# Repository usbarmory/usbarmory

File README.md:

Introduction
============

The USB armory is an open source hardware design, implementing a compact secure
computer.

This repository is aimed towards developers, if you wish to purchase a USB
armory board please see the [ordering information](https://github.com/usbarmory/usbarmory/wiki/Ordering-information).

Authors
=======

Andrea Barisani  
andrea@inversepath.com  

Andrej Rosano  
andrej@inversepath.com  

Daniele Bianco  
daniele@inversepath.com  

Documentation
=============

The main documentation can be found on the
[project wiki](https://github.com/usbarmory/usbarmory/wiki).

Board models
============

* [USB armory Mk II LAN](https://github.com/usbarmory/usbarmory/wiki/Mk-II-LAN)

* [USB armory Mk II](https://github.com/usbarmory/usbarmory/wiki/Mk-II-Introduction)

* USB armory Mk I

License
=======

USB armory | https://github.com/usbarmory/usbarmory  
Copyright (c) The USB armory authors

This is an open hardware design licensed under the terms of the CERN Open
Hardware Licence, see board revisions for applicable versions.

This source is distributed WITHOUT ANY EXPRESS OR IMPLIED WARRANTY, INCLUDING
OF MERCHANTABILITY, SATISFACTORY QUALITY AND FITNESS FOR A PARTICULAR PURPOSE.

Please see LICENSE files in each source subdirectory for applicable conditions.

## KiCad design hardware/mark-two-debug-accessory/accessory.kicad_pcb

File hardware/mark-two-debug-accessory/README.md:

USB armory Mk II debug accessory
================================

The USB armory is an open source hardware design, implementing a flash drive
sized computer.

The USB armory Mk II exposes a USB Type-C receptacle, which allows through the
so called USB-C 'debug accessory mode' to route analog/debug signals over its
connector, the USB armory Mk II design leverages on this to break out UART,
SPI, I²C, CAN (pre-transceiver), GPIOs connections to/from its application
processor.

The debug accessory board allows to access UART and GPIO signals through USB,
without requiring probes, through an FTDI FT4232H. This allows, for example,
access to the USB armory Mk II serial console without wires or probes, natively
using only USB cables. All other interfaces can be accessed through dedicated
breakout through holes.

This repository is aimed towards developers, if you wish to purchase a USB
armory board please see the [USB armory documentation](https://github.com/usbarmory/usbarmory/wiki).

PCB Information
===============

2 layers, 0.80mm thickness, top only components  
Outer layers 0.5 oz base copper foil  
Inner layers   1 oz base copper foil  
width (X) 45.65 mm, height (Y) 25.90 mm  
Red soldermask, white component legend

[Bill of materials](https://usbarmory.github.io/BOM/usbarmory-mark-two-debug-accessory.html)

DRC information
---------------

Minimum track width:            0.127 mm  
Minimum via diameter:           0.450 mm  
Outer layer track width:        0.127 mm  
Outer layer isolation distance: 0.127 mm  
Outer layer annular ring:       0.100 mm  
Smallest final hole (plated):   0.150 mm

Errata
------

The silkscreen labels for `3.3V` and `5V` are inverted on all rev v1 PCBs, see
this [issue](https://github.com/usbarmory/usbarmory/issues/68).

USB armory Mk II debug I/Os
===========================

*NOTE*: the connection between the debug accessory and the target is supported
only with the same orientation for both top layers (side with components for
the accessory, side with LEDs for the USB armory).

The following table summarizes the available configurations on the USB armory
Mk II through debug accessory mode, which are exposed on its Type-C receptacle
port.

|  USB-C pin   | MUX mode ALT0 | MUX mode ALT8 | MUX mode ALT2 | MUX mode ALT5 |
|:-------------|---------------|---------------|---------------|---------------|
| SSTXp1 (A2)  | UART2_TX      | ECSPI3_SSO¹   | I2C4_SCL¹     | GPIO1_IO20    |
| SSTXn1 (A3)  | UART2_RX      | ECSPI3_SCLK¹  | I2C4_SDA¹     | GPIO1_IO21    |
| SSRXp1 (B11) | UART2_RTS_B   | ECSPI3_MISO¹  | FLEXCAN2_RX¹  | GPIO1_IO23    |
| SSRXn1 (B10) | UART2_CTS_B   | ECSPI3_MOSI¹  | FLEXCAN2_TX¹  | GPIO1_IO22    |
| SSRXp2 (A11) | UART4_TX      | ECSPI2_SCLK   | I2C1_SCL      | GPIO1_IO28    |
| SSTXn2 (B3)  | UART4_RX      | ECSPI2_SSO    | I2C1_SDA      | GPIO1_IO29    |
| SSRXn2 (A10) | UART5_TX~     | ECSPI2_MOSI   | I2C2_SCL      | GPIO1_IO30    |
| SSTXp2 (B2)  | UART5_RX~     | ECSPI2_MISO   | I2C2_SDA      | GPIO1_IO31    |

¹ Only on USB armory Mk II boards mounting i.MX6UL SoC, not available on
  versions mounting the i.MX6ULZ.

Serial console
--------------

When running the [USB armory Debian base image](https://github.com/usbarmory/usbarmory-debian-base_image/releases)
the serial console (UART2) can be accessed, with the debug accessory jumper set to UART
position, as follows (example on Linux host with picocom):

```
picocom -b 115200 -eb /dev/ttyUSB2 --imap lfcrlf
```

Debug accessory jumper settings
===============================

Power source
------------

The debug accessory always acts as a power source and is meant to be connected
exclusively to the USB armory Mk II Type-C receptacle port. The USB armory Mk
II Type-C can be safely plugged on a different receptacle as the board can
handle two power sources simultaneously.

It is not recommended to connect the debug accessory to anything other than the
USB armory Mk II, however in case this happens compliant Type-C receptacles
should handle the situation gracefully¹ without concerns.

¹ USB Type-C Cable and Connector Specification (1.3, 2017-07-14):
  "Legacy hosts/chargers that by default source VBUS when connected using any
  legacy USB connector (Standard-A, Micro-B, etc.) to USB Type-C cable or adapter
  are exempted from these two requirements."

I/O mode
--------

The GPIO and UART functions can be used directly using the FTDI FT4232H USB
interface accessible on the Micro USB Type-B connector, all other modes can be
accessed using the exposed breakout through holes.

The following table illustrates the required jumper positions and interfaces
for each available I/O mode.

| Mode  | GPIO¹ | Interface
|:------|-------|-----------------------------------|
| GPIO  |  GPIO | FTDI MPSSE mode on [A,B]DBUS[4-7] |
| UART2 | !GPIO | FTDI RS232 mode on CDBUS[0-3]     |
| UART4 | !GPIO | FTDI RS232 mode on BDBUS[0-1]     |
| UART5 | !GPIO | FTDI RS232 mode on ADBUS[0-1]     |
| SPI2  |  N/A² | through holes: A11, B3, A10, B2   |
| SPI3  |  N/A² | through holes: A2,  A3, B11, B10  |
| I2C1  |  N/A² | through holes: A11, B3            |
| I2C2  |  N/A² | through holes: A10, B2            |
| I2C4  |  N/A² | through holes: A2,  A3            |
| CAN2  |  N/A² | through holes: B11, B10           |

¹ The GPIO header position refers to termination either of the two pins facing
  the "GPIO" label (GPIO position, pins towards positions 3 and 2) or the
  opposite position (!GPIO position, pins towards positions 2 and 1).

² Any position can be used as the FTDI is not used in such mode.

Pin assignment: GPIO
====================

|  USB-C pin   | i.MX6UL pin | FTDI pin | FTDI MPSSE |
|:-------------|-------------|----------|------------|
| SSTXp1 (A2)  | GPIO1_IO20  | BDBUS6   | #B GPIOL2  |
| SSTXn1 (A3)  | GPIO1_IO21  | BDBUS7   | #B GPIOL3  |
| SSRXp1 (B11) | GPIO1_IO23  | BDBUS5   | #B GPIOL1  |
| SSRXn1 (B10) | GPIO1_IO22  | BDBUS4   | #B GPIOL0  |
| SSRXp2 (A11) | GPIO1_IO28  | ADBUS4   | #A GPIOL0  |
| SSTXn2 (B3)  | GPIO1_IO29  | ADBUS7   | #A GPIOL3  |
| SSRXn2 (A10) | GPIO1_IO30  | ADBUS5   | #A GPIOL1  |
| SSTXp2 (B2)  | GPIO1_IO31  | ADBUS6   | #A GPIOL2  |

Pin assignment: UART2
=====================

|  USB-C pin   | i.MX6UL pin  | FTDI pin | FTDI MPSSE |
|:-------------|--------------|----------|------------|
| SSTXp1 (A2)  | UART2_TX     | CDBUS1   | #C RXD     |
| SSTXn1 (A3)  | UART2_RX     | CDBUS0   | #C TXD     |
| SSRXp1 (B11) | UART2_RTS_B¹ | CDBUS3   | #C CTS     |
| SSRXn1 (B10) | UART2_CTS_B¹ | CDBUS2   | #C RTS     |

¹ On USB armory Mk II rev. β see the [related errata](https://github.com/usbarmory/usbarmory/wiki/Errata-(Mk-II)#errata-inverted-uart-rtscts-signals-resolved-with-workaround).

Pin assignment: UART4
=====================

|  USB-C pin   | i.MX6UL pin | FTDI pin | FTDI MPSSE |
|:-------------|-------------|----------|------------|
| SSRXp2 (A11) | UART4_TX    | BDBUS1   | #B RXD     |
| SSTXn2 (B3)  | UART4_RX    | BDBUS0   | #B TXD     |

Pin assignment: UART5
=====================

|  USB-C pin   | i.MX6UL pin | FTDI pin | FTDI MPSSE |
|:-------------|-------------|----------|------------|
| SSRXn2 (A10) | UART5_TX    | ADBUS1   | #A RXD     |
| SSTXp2 (B2)  | UART5_RX    | ADBUS0   | #A TXD     |

Physical access: UART2
======================

When no debug accessory is available, the serial console (UART2) can be also
accessed with a USB-C plug breakout and a USB to 3.3 TTL serial cable with the
following configuration.

|  PIN   | Config          |
|:-------|-----------------|
| A4, A5 | 56 kOhm         |
| B4, B5 | 56 kOhm         |
| A2, A3 | 3.3V UART TX/RX |
| A4     | 5V              |
| A1     | GND             |

License
=======

USB armory | https://github.com/usbarmory/usbarmory  
Copyright (c) The USB armory authors

This is an open hardware design licensed under the terms of the CERN Open
Hardware Licence (OHL) v1.2.

You may redistribute and modify this documentation under the terms of the CERN
OHL v.1.2 (http://ohwr.org/cernohl). This documentation is distributed WITHOUT
ANY EXPRESS OR IMPLIED WARRANTY, INCLUDING OF MERCHANTABILITY, SATISFACTORY
QUALITY AND FITNESS FOR A PARTICULAR PURPOSE. Please see the CERN OHL v.1.2 for
applicable conditions.

The following exceptions apply:

- `../lib.snapeda`: all files in this directory are imported or modified
  from SnapEDA symbols and footprints, therefore the license at
  https://www.snapeda.com/about/FAQ/#license applies.

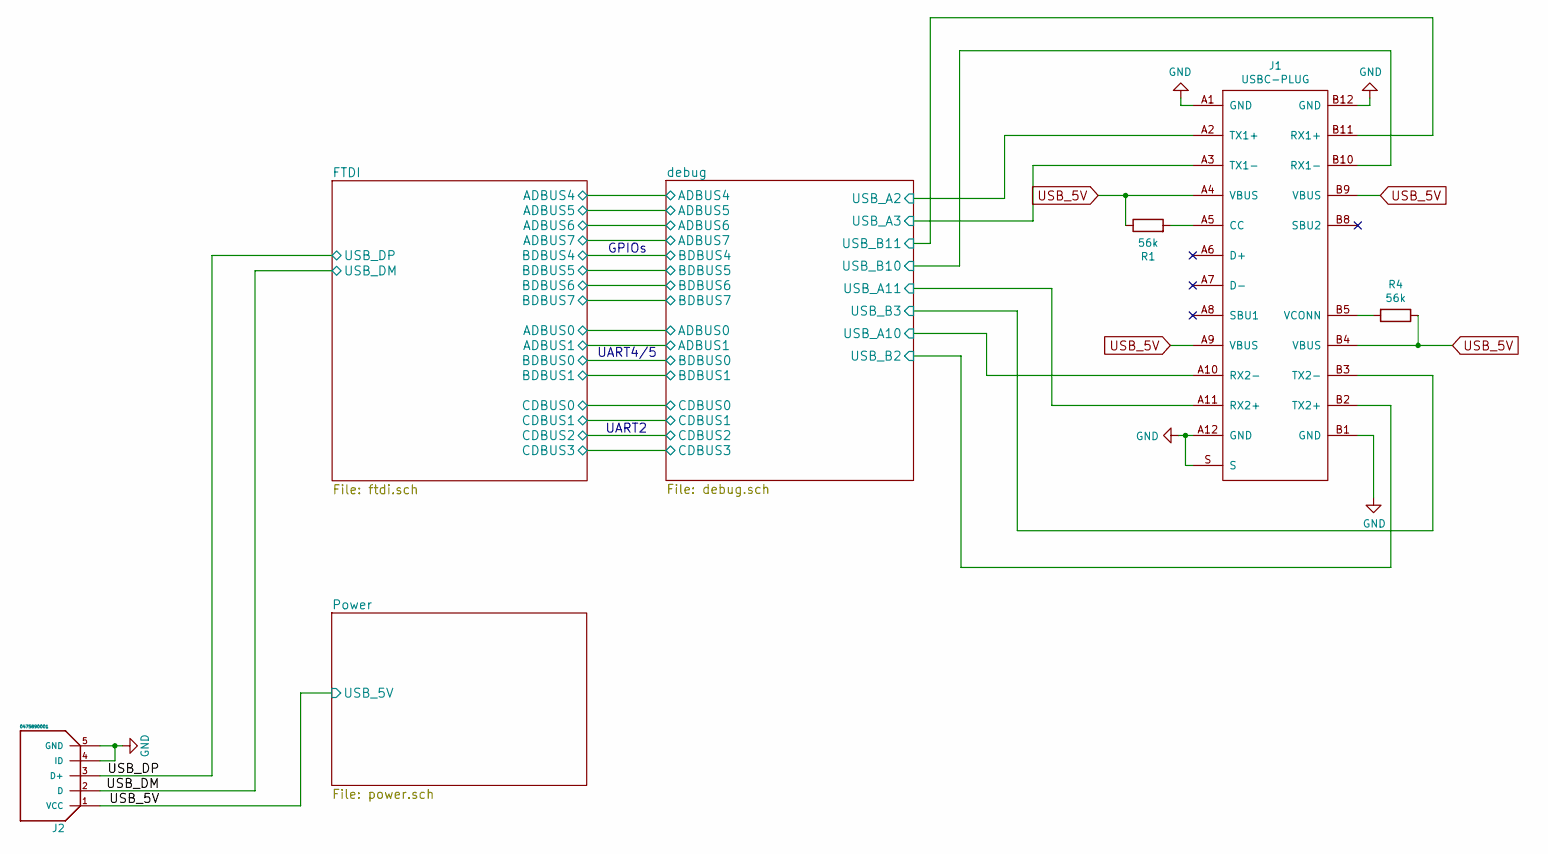
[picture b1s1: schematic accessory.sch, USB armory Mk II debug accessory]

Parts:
J1: USBC-PLUG; WURTH_632712000011; Mfg PN 632712000011
J2: 0475890001; MOLEX_0475890001; Mfg PN 0475890001
R1, R4: 56k; SM0603; Mfg PN MCT06030C5602FP500

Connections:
/USB_DM: J2.2 (D); also elsewhere on the board
/USB_DP: J2.3 (D+); also elsewhere on the board
/debug/USB_A2: J1.A2 (TX1+); also elsewhere on the board
/debug/USB_A3: J1.A3 (TX1-); also elsewhere on the board
/debug/USB_A10: J1.A10 (RX2-); also elsewhere on the board
/debug/USB_A11: J1.A11 (RX2+); also elsewhere on the board
/debug/USB_B2: J1.B2 (TX2+); also elsewhere on the board
/debug/USB_B3: J1.B3 (TX2-); also elsewhere on the board
/debug/USB_B10: J1.B10 (RX1-); also elsewhere on the board
/debug/USB_B11: J1.B11 (RX1+); also elsewhere on the board
GND: J1.A1 (GND), J1.A12 (GND), J1.B1 (GND), J1.B12 (GND), J1.S, J2.4 (ID), J2.5 (GND); also elsewhere on the board
unnamed: J1.A5 (CC), R1.2
unnamed: J1.B5 (VCONN), R4.2
USB_5V: J1.A4 (VBUS), J1.A9 (VBUS), J1.B4 (VBUS), J1.B9 (VBUS), J2.1 (VCC), R1.1, R4.1; also elsewhere on the board

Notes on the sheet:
GPIOs
UART4/5
UART2

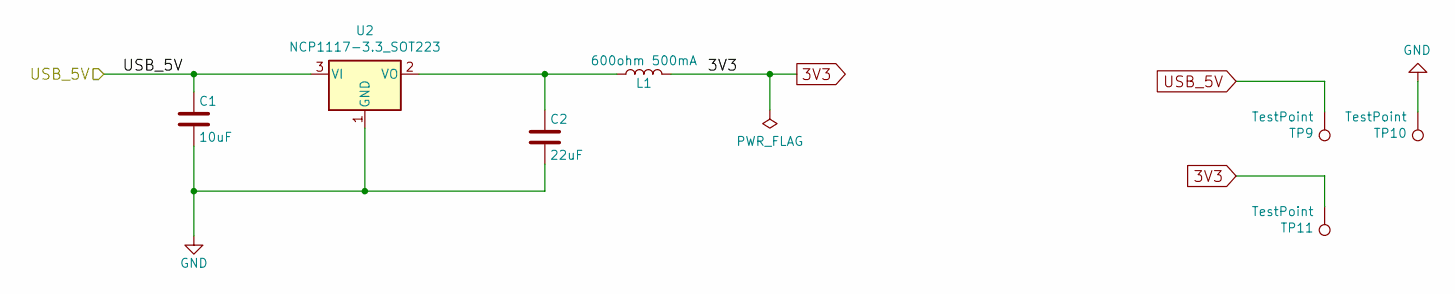
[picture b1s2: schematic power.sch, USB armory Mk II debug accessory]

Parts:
C1: 10uF; SM0603; Mfg PN C1608X5R1A106M080AC
C2: 22uF; SM0603; Mfg PN C1608X5R1A226M080AC
L1: 600ohm 500mA; SM0603; Mfg PN BLM18AG601SN1D
TP9, TP10, TP11: TestPoint; CONN_1
U2: NCP1117-3.3_SOT223; SOT-223; Mfg PN NCP1117ST33T3G

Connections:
3V3: L1.2, TP11.1; also elsewhere on the board
GND: C1.2, C2.2, TP10.1, U2.1 (GND); also elsewhere on the board
unnamed: C2.1, L1.1, U2.2 (VO)
USB_5V: C1.1, TP9.1, U2.3 (VI); also elsewhere on the board

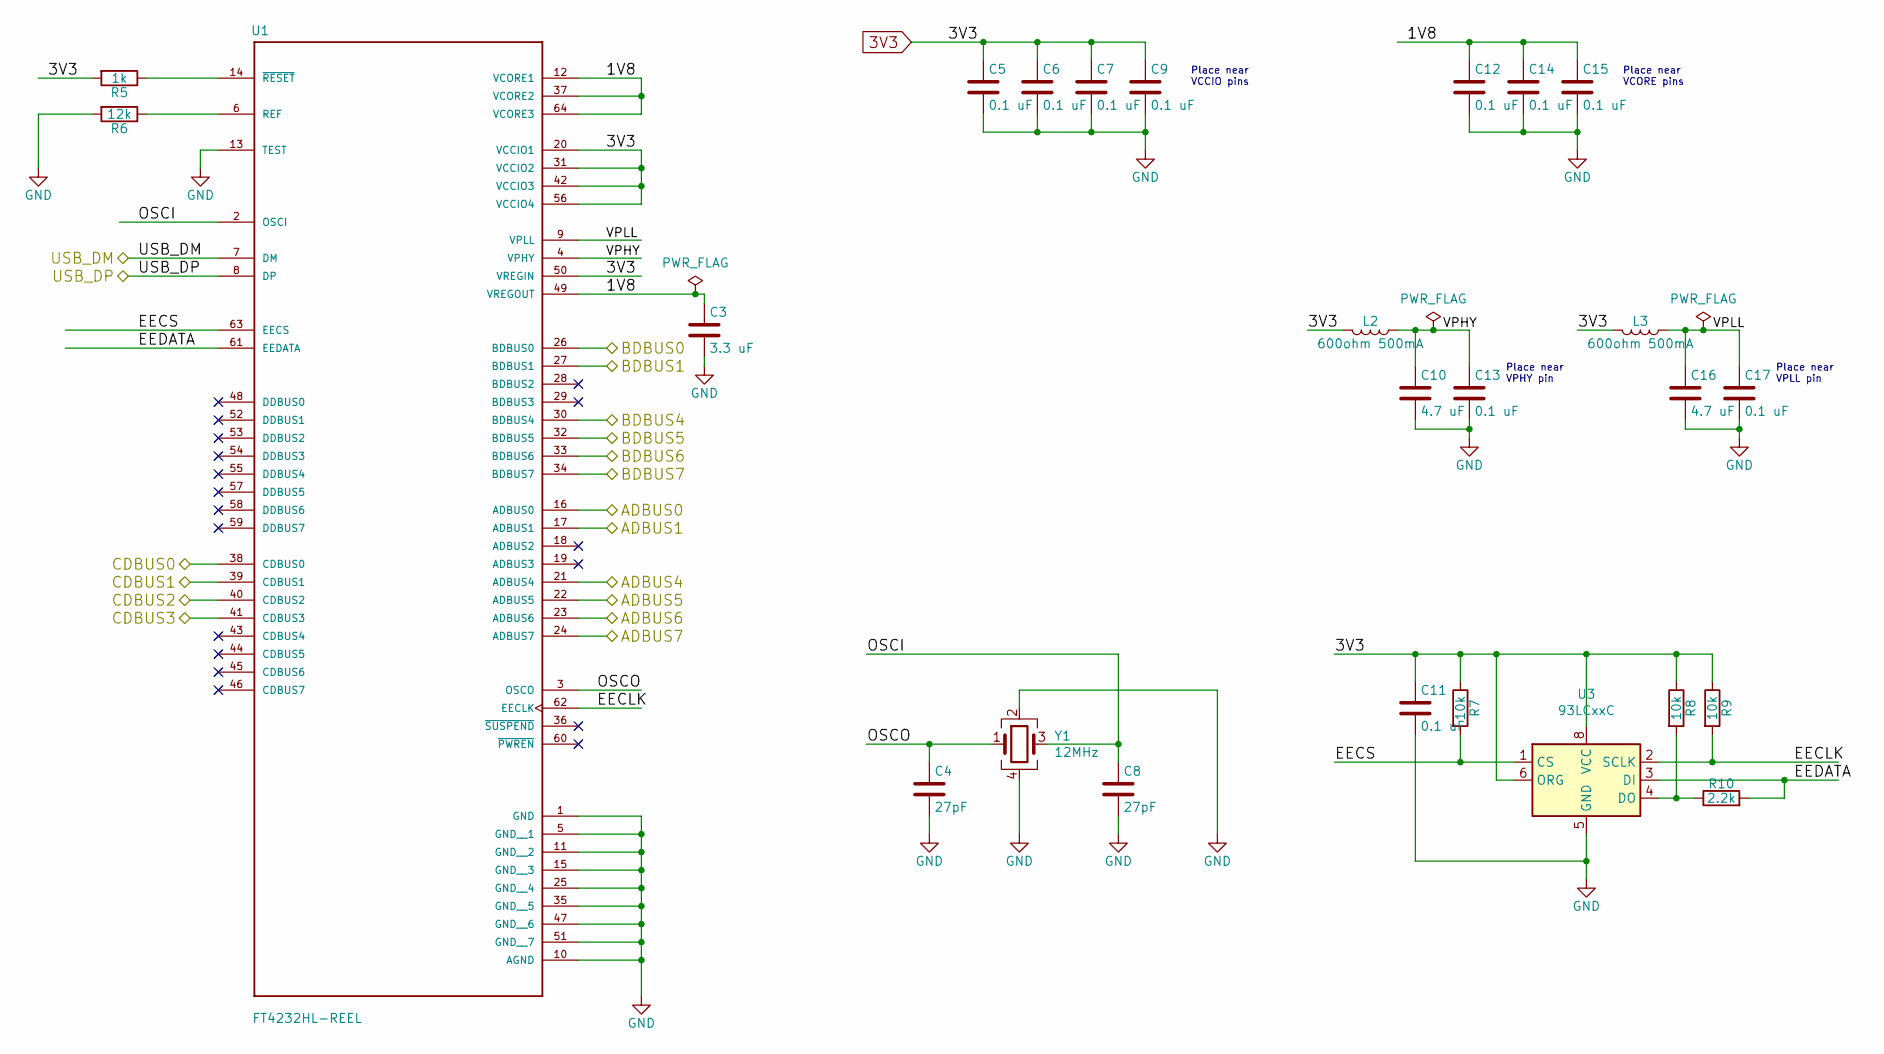
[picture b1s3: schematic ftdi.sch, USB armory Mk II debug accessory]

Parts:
C3: 3.3 uF; SM0603; Mfg PN C1608X5R1C335K080AC
C4, C8: 27pF; SM0603; Mfg PN GRM1885C1H270FA01D
C5, C6, C7, C9, C11, C12, C13, C14, C15, C17: 0.1 uF; SM0603; Mfg PN C1608X7R1E104K080AA
C10, C16: 4.7 uF; SM0603; Mfg PN CGB3B1X5R1A475M055AC
L2, L3: 600ohm 500mA; SM0603; Mfg PN BLM18AG601SN1D
R5: 1k; SM0603; Mfg PN RCA06031K00FKEAHP
R6: 12k; SM0603; Mfg PN CRCW060312K0FKEAC
R7, R8, R9: 10k; SM0603; Mfg PN CRCW060310K0FKEA
R10: 2.2k; SM0603; Mfg PN RCS06032K20JNEA
U1: FT4232HL-REEL; QFP50P1200X1200X160-64N; Mfg PN FT4232HL-REEL
U3: 93LCxxC; 8L_SOIC_Narrow_3_90_SN_C04-057C; Mfg PN 93LC56C-I/SN
Y1: 12MHz; TXC-3.2x2.5; Mfg PN 7M-12.000MAAJ-T

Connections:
3V3: C5.1, C6.1, C7.1, C9.1, C11.1, L2.1, L3.1, R5.2, R7.1, R8.1, R9.1, U1.20 (VCCIO1), U1.31 (VCCIO2), U1.42 (VCCIO3), U1.50 (VREGIN), U1.56 (VCCIO4), U3.6 (ORG), U3.8 (VCC); also elsewhere on the board
/FTDI/1V8: C3.1, C12.1, C14.1, C15.1, U1.12 (VCORE1), U1.37 (VCORE2), U1.49 (VREGOUT), U1.64 (VCORE3)
/FTDI/ADBUS0: U1.16 (ADBUS0); also elsewhere on the board
/FTDI/ADBUS1: U1.17 (ADBUS1); also elsewhere on the board
/FTDI/ADBUS4: U1.21 (ADBUS4); also elsewhere on the board
/FTDI/ADBUS5: U1.22 (ADBUS5); also elsewhere on the board
/FTDI/ADBUS6: U1.23 (ADBUS6); also elsewhere on the board
/FTDI/ADBUS7: U1.24 (ADBUS7); also elsewhere on the board
/FTDI/BDBUS0: U1.26 (BDBUS0); also elsewhere on the board
/FTDI/BDBUS1: U1.27 (BDBUS1); also elsewhere on the board
/FTDI/BDBUS4: U1.30 (BDBUS4); also elsewhere on the board
/FTDI/BDBUS5: U1.32 (BDBUS5); also elsewhere on the board
/FTDI/BDBUS6: U1.33 (BDBUS6); also elsewhere on the board
/FTDI/BDBUS7: U1.34 (BDBUS7); also elsewhere on the board
/FTDI/CDBUS0: U1.38 (CDBUS0); also elsewhere on the board
/FTDI/CDBUS1: U1.39 (CDBUS1); also elsewhere on the board
/FTDI/CDBUS2: U1.40 (CDBUS2); also elsewhere on the board
/FTDI/CDBUS3: U1.41 (CDBUS3); also elsewhere on the board
/FTDI/EECLK: R9.2, U1.62 (EECLK), U3.2 (SCLK)
/FTDI/EECS: R7.2, U1.63 (EECS), U3.1 (CS)
/FTDI/EEDATA: R10.2, U1.61 (EEDATA), U3.3 (DI)
/FTDI/OSCI: C8.1, U1.2 (OSCI), Y1.3
/FTDI/OSCO: C4.1, U1.3 (OSCO), Y1.1
/FTDI/VPHY: C10.1, C13.1, L2.2, U1.4 (VPHY)
/FTDI/VPLL: C16.1, C17.1, L3.2, U1.9 (VPLL)
/USB_DM: U1.7 (DM); also elsewhere on the board
/USB_DP: U1.8 (DP); also elsewhere on the board
GND: C3.2, C4.2, C5.2, C6.2, C7.2, C8.2, C9.2, C10.2, C11.2, C12.2, C13.2, C14.2, C15.2, C16.2, C17.2, R6.2, U1.1 (GND), U1.5 (GND__1), U1.10 (AGND), U1.11 (GND__2), U1.13 (TEST), U1.15 (GND__3), U1.25 (GND__4), U1.35 (GND__5), U1.47 (GND__6), U1.51 (GND__7), U3.5 (GND), Y1.2, Y1.4; also elsewhere on the board
unnamed: R5.1, U1.14 (~RESET~)
unnamed: R6.1, U1.6 (REF)
unnamed: R8.2, R10.1, U3.4 (DO)

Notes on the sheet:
Place near VCORE pins
Place near VCCIO pins
Place near VPLL pin
Place near VPHY pin

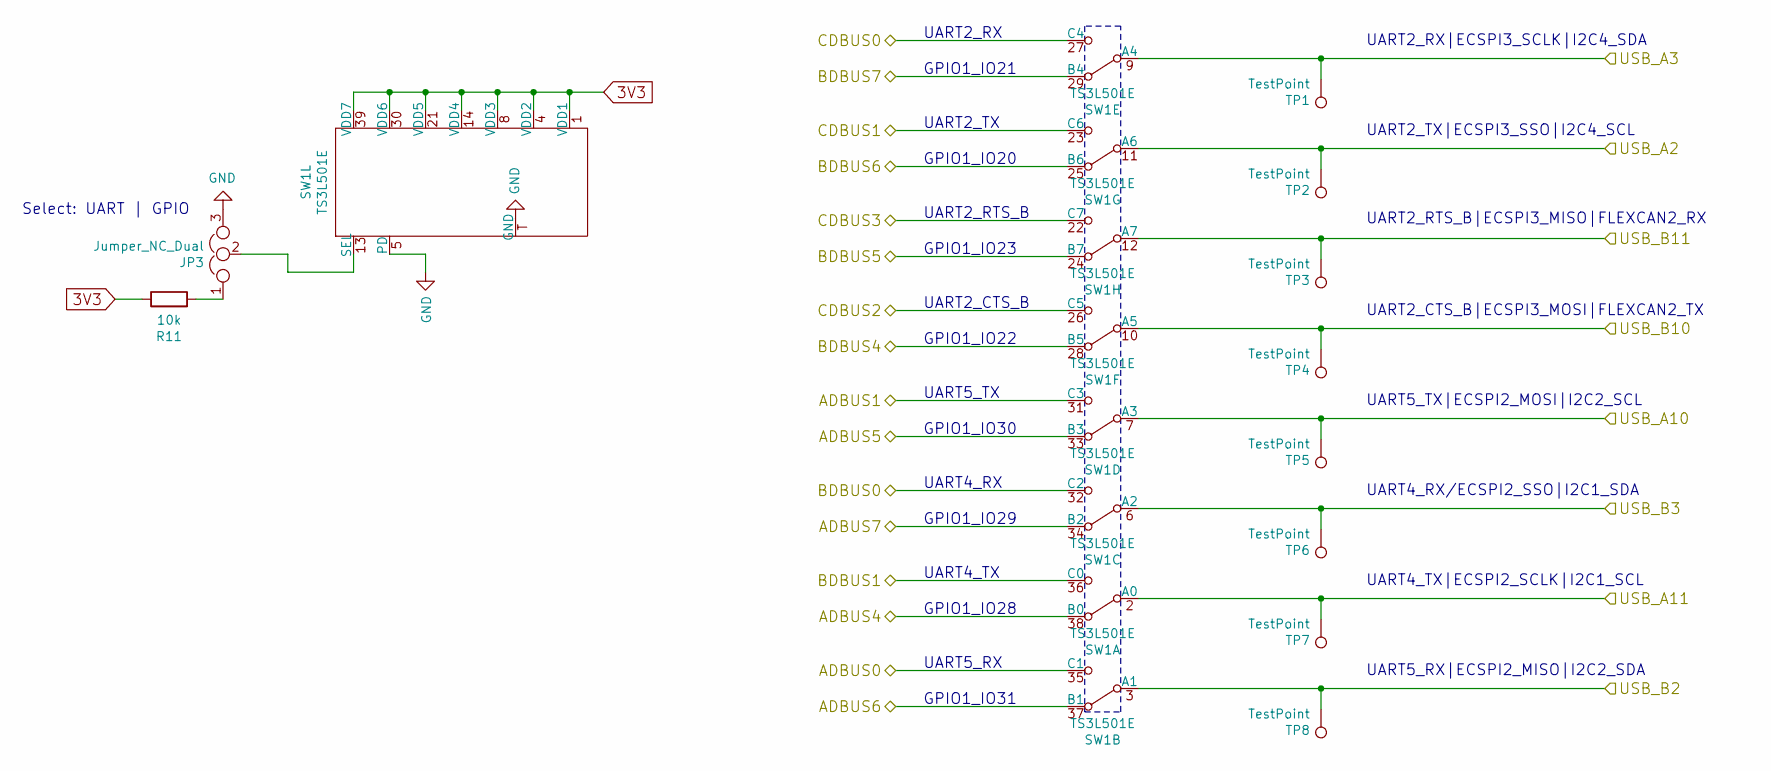
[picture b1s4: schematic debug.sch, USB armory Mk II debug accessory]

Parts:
JP3: Jumper_NC_Dual; SIL-3; Mfg PN 68000-103HLF
R11: 10k; SM0603; Mfg PN CRCW060310K0FKEA
SW1: TS3L501E; R-PWQFN-N42
TP1, TP2, TP3, TP4, TP5, TP6, TP7, TP8: TestPoint; CONN_1

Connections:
3V3: R11.1, SW1.1 (VDD1), SW1.4 (VDD2), SW1.8 (VDD3), SW1.14 (VDD4), SW1.21 (VDD5), SW1.30 (VDD6), SW1.39 (VDD7); also elsewhere on the board
/FTDI/ADBUS0: SW1.35 (C1); also elsewhere on the board
/FTDI/ADBUS1: SW1.31 (C3); also elsewhere on the board
/FTDI/ADBUS4: SW1.38 (B0); also elsewhere on the board
/FTDI/ADBUS5: SW1.33 (B3); also elsewhere on the board
/FTDI/ADBUS6: SW1.37 (B1); also elsewhere on the board
/FTDI/ADBUS7: SW1.34 (B2); also elsewhere on the board
/FTDI/BDBUS0: SW1.32 (C2); also elsewhere on the board
/FTDI/BDBUS1: SW1.36 (C0); also elsewhere on the board
/FTDI/BDBUS4: SW1.28 (B5); also elsewhere on the board
/FTDI/BDBUS5: SW1.24 (B7); also elsewhere on the board
/FTDI/BDBUS6: SW1.25 (B6); also elsewhere on the board
/FTDI/BDBUS7: SW1.29 (B4); also elsewhere on the board
/FTDI/CDBUS0: SW1.27 (C4); also elsewhere on the board
/FTDI/CDBUS1: SW1.23 (C6); also elsewhere on the board
/FTDI/CDBUS2: SW1.26 (C5); also elsewhere on the board
/FTDI/CDBUS3: SW1.22 (C7); also elsewhere on the board
/debug/USB_A2: SW1.11 (A6), TP2.1; also elsewhere on the board
/debug/USB_A3: SW1.9 (A4), TP1.1; also elsewhere on the board
/debug/USB_A10: SW1.7 (A3), TP5.1; also elsewhere on the board
/debug/USB_A11: SW1.2 (A0), TP7.1; also elsewhere on the board
/debug/USB_B2: SW1.3 (A1), TP8.1; also elsewhere on the board
/debug/USB_B3: SW1.6 (A2), TP6.1; also elsewhere on the board
/debug/USB_B10: SW1.10 (A5), TP4.1; also elsewhere on the board
/debug/USB_B11: SW1.12 (A7), TP3.1; also elsewhere on the board
GND: JP3.3, SW1.5 (PD), SW1.T (GND); also elsewhere on the board
unnamed: JP3.1, R11.2
unnamed: JP3.2, SW1.13 (SEL)

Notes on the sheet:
UART2_CTS_B|ECSPI3_MOSI|FLEXCAN2_TX
UART5_TX|ECSPI2_MOSI|I2C2_SCL
UART4_RX/ECSPI2_SSO|I2C1_SDA
UART4_TX|ECSPI2_SCLK|I2C1_SCL
UART5_RX|ECSPI2_MISO|I2C2_SDA
UART2_RTS_B|ECSPI3_MISO|FLEXCAN2_RX
UART2_TX|ECSPI3_SSO|I2C4_SCL
UART2_RX|ECSPI3_SCLK|I2C4_SDA
GPIO1_IO20
GPIO1_IO21
UART2_RX
UART2_TX
UART2_RTS_B
UART2_CTS_B
UART5_TX
UART4_RX
Select: UART | GPIO
UART4_TX
UART5_RX
GPIO1_IO23
GPIO1_IO22
GPIO1_IO30
GPIO1_IO29
GPIO1_IO28
GPIO1_IO31

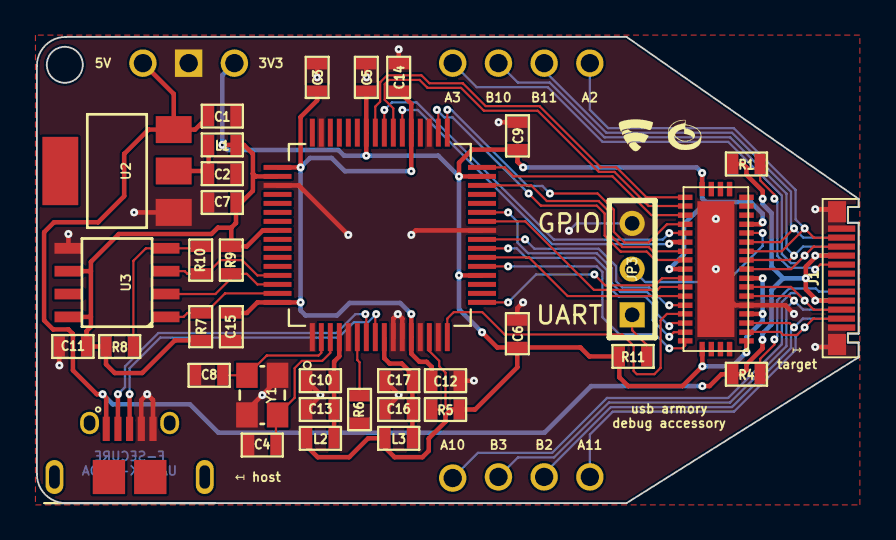
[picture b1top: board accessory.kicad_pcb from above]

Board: 2 copper layers, 45.7 x 25.9 mm, 50 parts (0 on the bottom side), 45 nets.

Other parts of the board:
FSC_LOGO_NO_TEXT_SMALL: G***; FSC_LOGO_NO_TEXT_SMALL
Ref**: Val**; IP_LOGO_NO_TEXT_SMALL

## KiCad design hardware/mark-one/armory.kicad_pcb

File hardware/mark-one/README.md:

Introduction
============

The USB armory is an open source hardware design, implementing a flash drive
sized computer.

This repository is aimed towards developers, if you wish to purchase a USB
armory board please see the [ordering information](https://github.com/usbarmory/usbarmory/wiki/Ordering-information).

Authors
=======

Andrea Barisani  
andrea@inversepath.com  

Andrej Rosano  
andrej@inversepath.com  

Daniele Bianco  
daniele@inversepath.com  

Revision information
====================

This directory contains the hardware design for the USB armory board, first
revision (Mark I).

Current schematics and layout files have been designed in KiCad (`release
2014-01-25 - 0.201403191418+4754~10~ubuntu12.04.1`)

PCB information
===============

6 layers, 2.00mm thickness  
Outer layers 0.5 oz base copper foil  
Inner layers   1 oz base copper foil  
width (X) 65.6 mm, height (Y) 19.5 mm  
Electroless Nickel Immersion Gold (ENIG) surface finish  
Selective hard gold (min 0.75um) plating for J2 (USB)  
Black resist, white component legend

Layers
------

Order and type of copper layers:  
  TOP:         signal, front components  
  SIGNAL 1:    signal  
  GND POWER 1: ground and power plane  
  GND POWER 2: ground and power plane  
  SIGNAL 2:    signal  
  BOTTOM:      signal, back components  

| Layer | Description               |  Thickness (in um)  |
|:-----:|---------------------------|:-------------------:|
|       | LPI mask                  |   15                |
|       | ENIG plating              |   18                |
|   1   | copper                    |   17                |
|       | prepreg, 3 x PP 1080      |  240 -> 220         |
|   2   | copper                    |   35                |
|       | core, FR4  35/35          |  300                |
|   3   | copper                    |   35                |
|       | prepreg, 4 x PP 7628      |  760 -> 720         |
|   4   | copper                    |   35                |
|       | core, FR4  35/35          |  300                |
|   5   | copper                    |   35                |
|       | prepreg, 3 x PP 1080      |  240 -> 220         |
|   6   | copper                    |   17                |
|       | ENIG plating              |   18                |
|       | LPI mask                  |   15                |

Material: Isola PCL370-HR
Total thickness: 2.0 mm

DRC information
---------------

Minimum track width:            0.127 mm  
Minimum via diameter:           0.406 mm  
Outer layer track width:        0.127 mm  
Outer layer isolation distance: 0.127 mm  
Outer layer annular ring:       0.075 mm  
Inner layer track width:        0.127 mm  
Inner layer isolation distance: 0.127 mm  
Inner layer annular ring:       0.075 mm  
Smallest final hole (plated):   0.150 mm

Regulatory compliance & handling
================================

The USB armory board is intended for use as a development platform for hardware
or software. The board is an open system design, which does not include a
shielded enclosure. This may cause interference to other electrical or
electronic devices in close proximity. In a domestic environment, this product
may cause radio interference in which case the user may be required to take
adequate measures. In addition, this board should not be used near any medical
equipment or RF devices.

The board is sensitive to ESD. Hold the board only by its edges. After removing
the board from its box, place it on a grounded, static-free surface.

The board can become hot, like any fan-less design, during continuous high CPU
loads, mind its temperature while handling it.

License
=======

USB armory | https://github.com/usbarmory/usbarmory  
Copyright (c) The USB armory authors

This is an open hardware design licensed under the terms of the CERN Open
Hardware Licence (OHL) v1.2.

You may redistribute and modify this documentation under the terms of the CERN
OHL v.1.2 (http://ohwr.org/cernohl). This documentation is distributed WITHOUT
ANY EXPRESS OR IMPLIED WARRANTY, INCLUDING OF MERCHANTABILITY, SATISFACTORY
QUALITY AND FITNESS FOR A PARTICULAR PURPOSE. Please see the CERN OHL v.1.2 for
applicable conditions.

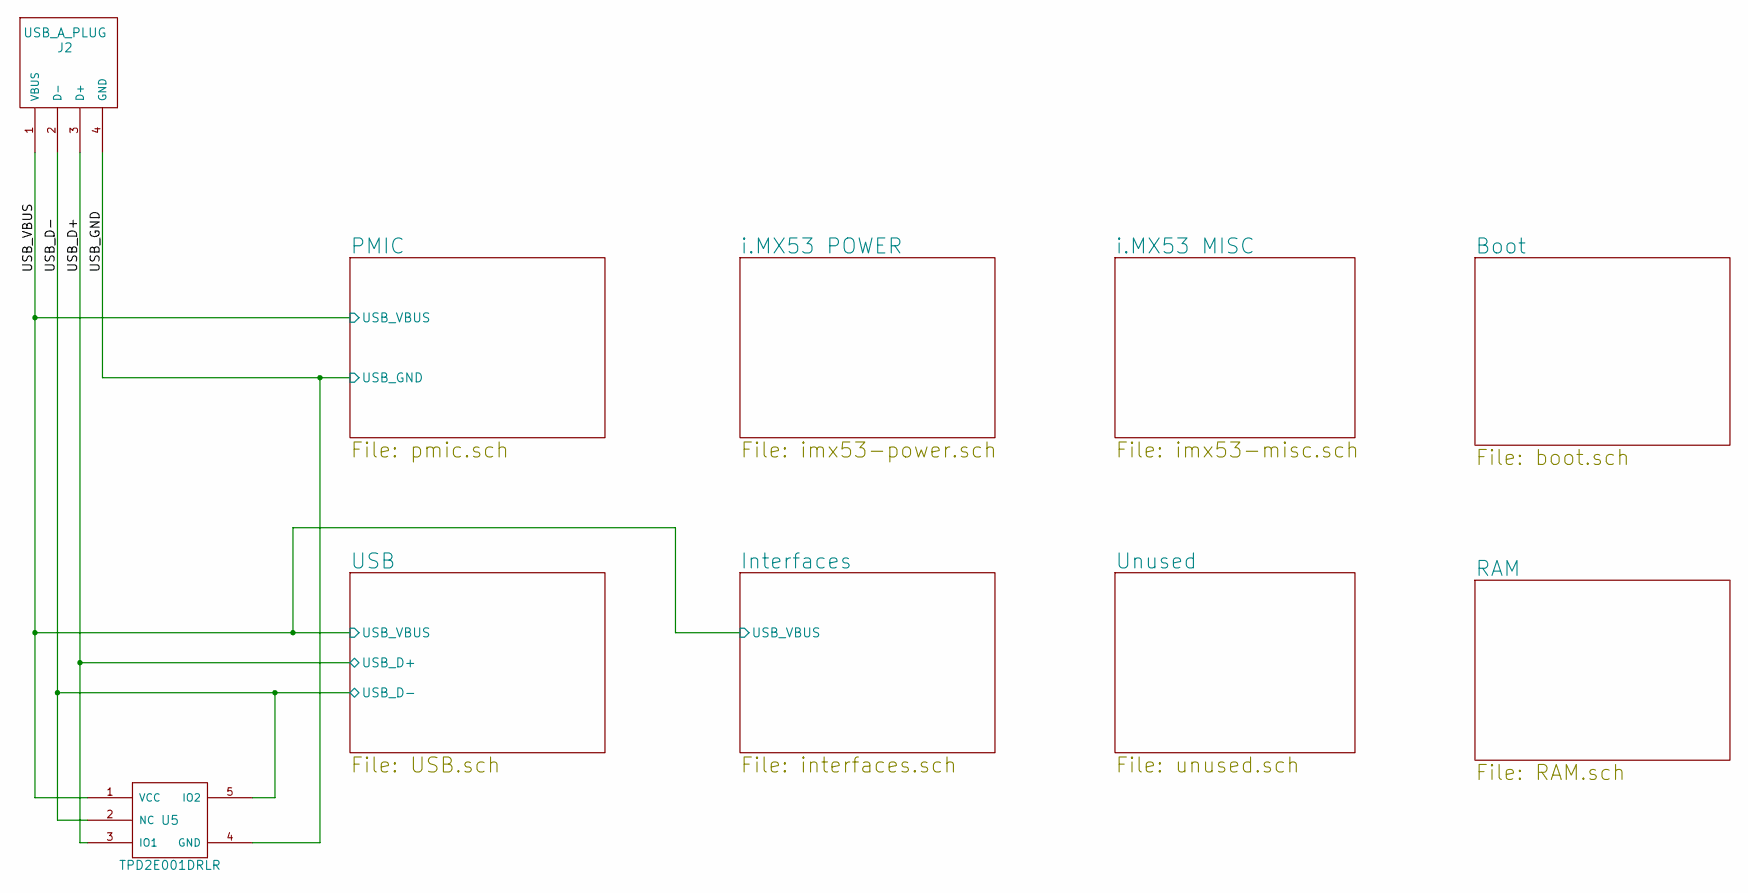
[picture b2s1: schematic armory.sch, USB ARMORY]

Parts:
J2: USB_A_PLUG; usb-PCB
U5: TPD2E001DRLR; R-PDSO-N5; Mfg PN TPD2E001DRLR

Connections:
/Interfaces/USB_VBUS: J2.1 (VBUS), U5.1 (VCC); also elsewhere on the board
/USB/USB_D+: J2.3 (D+), U5.3 (IO1); also elsewhere on the board
/USB/USB_D-: J2.2 (D-), U5.2 (NC), U5.5 (IO2); also elsewhere on the board
GND: J2.4 (GND), U5.4 (GND); also elsewhere on the board

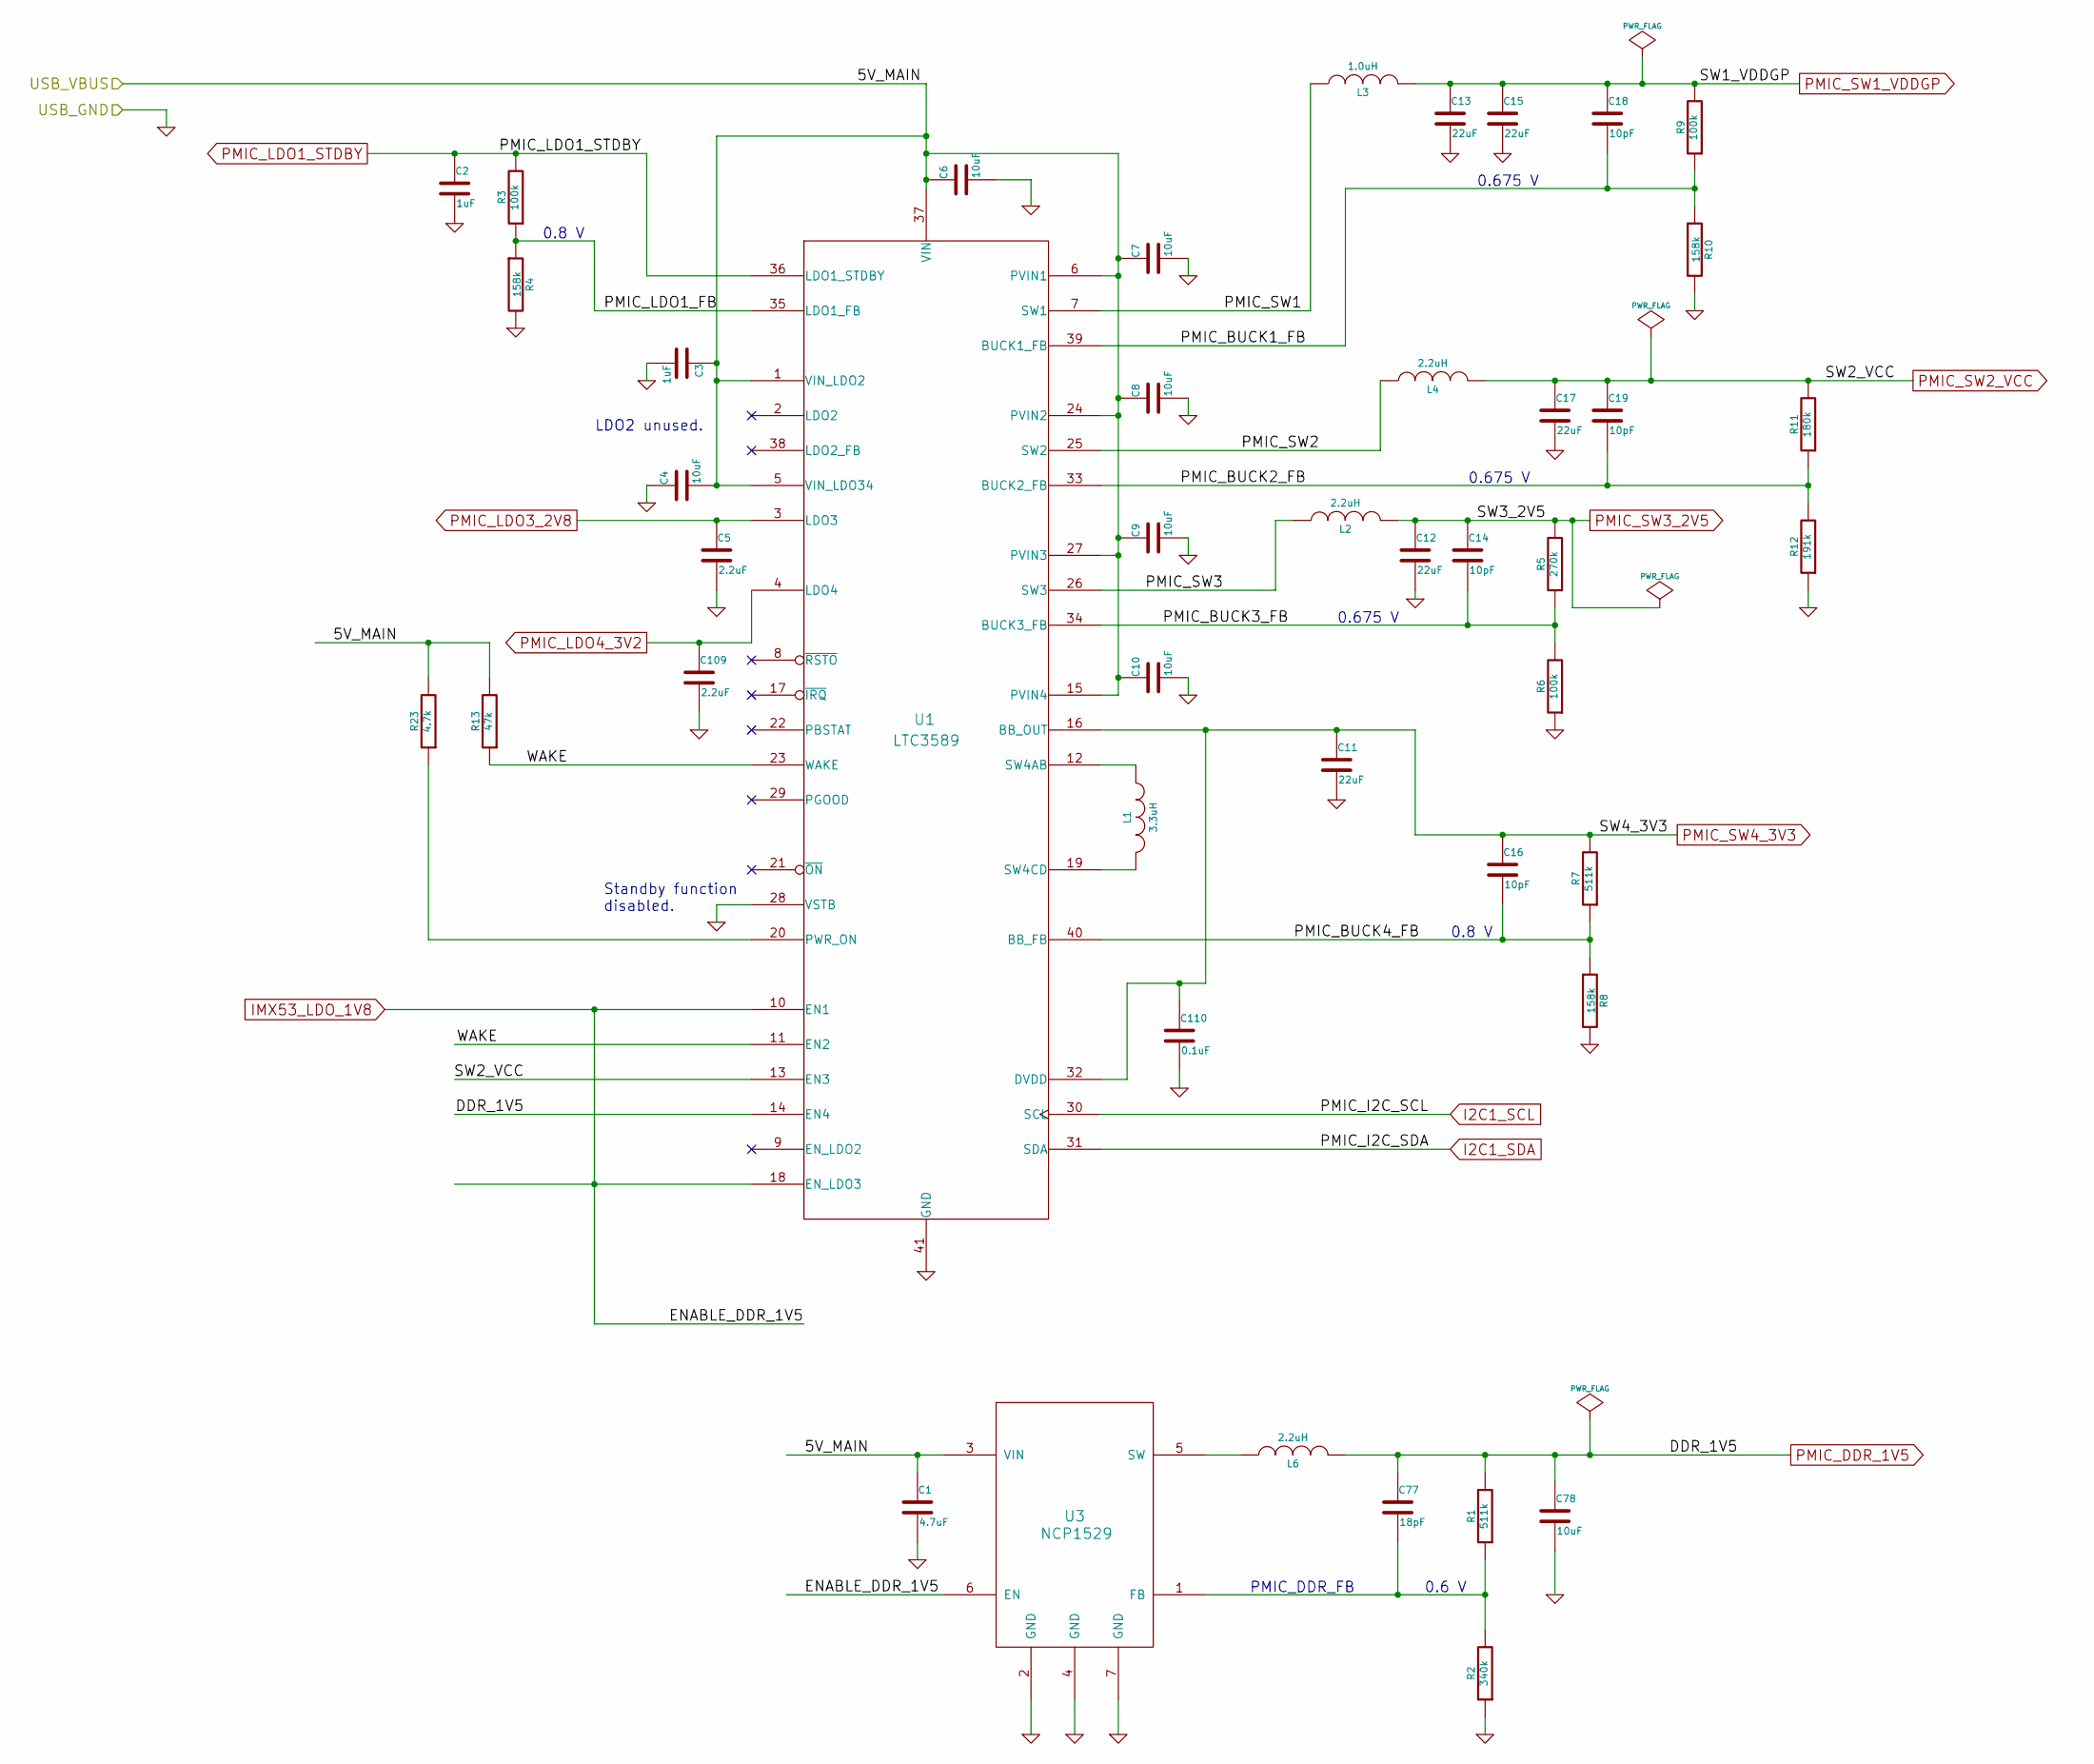
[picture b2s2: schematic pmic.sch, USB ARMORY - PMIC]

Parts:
C1: 4.7uF; SM0603; Mfg PN CGB3B1X5R1A475K055AC
C2, C3: 1uF; SM0201; Mfg PN C0603X5R0J105M030BC
C4, C6, C7, C8, C9, C10, C78: 10uF; SM0603; Mfg PN C1608X5R1A106K080AC
C5, C109: 2.2uF; SM0402; Mfg PN C1005X5R0J225K050BC
C11, C12, C13, C15, C17: 22uF; SM0603; Mfg PN C1608X5R0J226M080AC
C14, C16, C18, C19: 10pF; SM0402; Mfg PN 04025U100JAT2A
C77: 18pF; SM0201; Mfg PN C0603C0G1H180J030BA
C110: 0.1uF; SM0201; Mfg PN C0603X5R0J104K030BC
L1: 3.3uH; VLS252012ET; Mfg PN VLS252012ET-3R3M
L2, L4, L6: 2.2uH; VLS252012ET; Mfg PN VLS252012ET-2R2M
L3: 1.0uH; VLS252012ET; Mfg PN VLS252012ET-1R0N
R1, R7: 511k; SM0201; Mfg PN CRCW0201511KFNED
R2: 340k; SM0201; Mfg PN CRCW0201340KFNED
R3, R6, R9: 100k; SM0201; Mfg PN CRCW0201100KFNED
R4, R8, R10: 158k; SM0201; Mfg PN CRCW0201158KFNED
R5: 270k; SM0201; Mfg PN CRCW0201270KFNED
R11: 180k; SM0201; Mfg PN CRCW0201180KFNED
R12: 191k; SM0201; Mfg PN CRCW0201191KFNED
R13: 47k; SM0201; Mfg PN CRCW020147K0FNED
R23: 4.7k; SM0201; Mfg PN CRCW02014K70FNED
U1: LTC3589; ltc3589-QFN40; Mfg PN LTC3589EUJ-2#PBF
U3: NCP1529; Mfg PN NCP1529MUTBG

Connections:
/Interfaces/USB_VBUS: C1.1, C3.1, C4.2, C6.1, C7.1, C8.1, C9.1, C10.1, R13.2, R23.2, U1.1 (VIN_LDO2), U1.5 (VIN_LDO34), U1.6 (PVIN1), U1.15 (PVIN4), U1.24 (PVIN2), U1.27 (PVIN3), U1.37 (VIN), U3.3 (VIN); also elsewhere on the board
/PMIC/PMIC_BUCK1_FB: C18.2, R9.1, R10.1, U1.39 (BUCK1_FB)
/PMIC/PMIC_BUCK2_FB: C19.2, R11.1, R12.2, U1.33 (BUCK2_FB)
/PMIC/PMIC_BUCK3_FB: C14.2, R5.1, R6.2, U1.34 (BUCK3_FB)
/PMIC/PMIC_BUCK4_FB: C16.2, R7.1, R8.1, U1.40 (BB_FB)
/PMIC/PMIC_LDO1_FB: R3.1, R4.1, U1.35 (LDO1_FB)
/PMIC/PMIC_SW1: L3.1, U1.7 (SW1)
/PMIC/PMIC_SW2: L4.1, U1.25 (SW2)
/PMIC/PMIC_SW3: L2.1, U1.26 (SW3)
/PMIC/WAKE: R13.1, U1.11 (EN2), U1.23 (WAKE)
GND: C1.2, C2.2, C3.2, C4.1, C5.2, C6.2, C7.2, C8.2, C9.2, C10.2, C11.2, C12.2, C13.2, C15.2, C17.2, C78.2, C109.2, C110.2, R2.1, R4.2, R6.1, R8.2, R10.2, R12.1, U1.28 (VSTB), U1.41 (GND), U3.2 (GND), U3.4 (GND), U3.7 (GND); also elsewhere on the board
I2C1_SCL: U1.30 (SCL); also elsewhere on the board
I2C1_SDA: U1.31 (SDA); also elsewhere on the board
IMX53_LDO_1V8: U1.10 (EN1), U1.18 (EN_LDO3), U3.6 (EN); also elsewhere on the board
unnamed: C77.2, R1.1, R2.2, U3.1 (FB)
unnamed: L1.1, U1.12 (SW4AB)
unnamed: L1.2, U1.19 (SW4CD)
unnamed: L6.1, U3.5 (SW)
unnamed: R23.1, U1.20 (PWR_ON)
PMIC_DDR_1V5: C77.1, C78.1, L6.2, R1.2, U1.14 (EN4); also elsewhere on the board
PMIC_LDO1_STDBY: C2.1, R3.2, U1.36 (LDO1_STDBY); also elsewhere on the board
PMIC_LDO3_2V8: C5.1, U1.3 (LDO3); also elsewhere on the board
PMIC_LDO4_3V2: C109.1, U1.4 (LDO4); also elsewhere on the board
PMIC_SW1_VDDGP: C13.1, C15.1, C18.1, L3.2, R9.2; also elsewhere on the board
PMIC_SW2_VCC: C17.1, C19.1, L4.2, R11.2, U1.13 (EN3); also elsewhere on the board
PMIC_SW3_2V5: C12.1, C14.1, L2.2, R5.2; also elsewhere on the board
PMIC_SW4_3V3: C11.1, C16.1, C110.1, R7.2, U1.16 (BB_OUT), U1.32 (DVDD); also elsewhere on the board

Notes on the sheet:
Standby function disabled.
0.8 V
0.675 V
LDO2 unused.
0.6 V
PMIC_DDR_FB

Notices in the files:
armory-alpha/USB.sch:
Copyright © 2014 Inverse Path S.r.l.
License: GNU General Public License, version 2
hardware/alpha/RAM.sch:
License: CERN OHL v1.2
hardware/mark-two/armory.kicad_pcb:
License: CERN-OHL-S
